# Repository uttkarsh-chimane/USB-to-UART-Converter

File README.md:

<h1 align="center">💡 USB Type-C to UART Converter</h1>

---

## ⚙️ What I Built

A compact, production-style USB-to-UART bridge designed in KiCad using the CP2102N USB-to-serial interface IC.

The board enables reliable serial communication between a host PC and embedded systems for debugging, firmware flashing, and data exchange. It is designed as a plug-and-play development tool that replaces generic USB-to-UART adapters with a cleaner, integrated hardware solution.

--- 

## 🚀 Overview

This project implements a robust USB-to-UART hardware interface using a USB Type-C connector and the CP2102N USB bridge IC.

---

## 📷 Project Gallery

🧩 **3D PCB Render**

Final assembled board visualization from KiCad 3D viewer.

🟠 **PCB Layout – Top Copper**

Top layer routing showing USB interface, CP2102N placement, and signal routing.

.png)

🔵 **PCB Layout – Bottom Copper**

Bottom layer used for ground plane and signal return integrity.

.png)

⚙️ **Schematic – Power Section**

Power input stage including USB VBUS handling, decoupling, and regulation strategy.

🔌 **Schematic – USB Interface Section**

USB Type-C interface with CC resistors, ESD protection, and data routing.

📡 **Schematic – UART Interface Section**

CP2102N UART communication block with TX/RX routing and headers.

---

## ✨ Features

* USB Type-C interface (USB 2.0)
* CP2102N USB-to-UART bridge IC
* TX/RX UART communication support
* RX/TX status indicator LEDs
* USB data line ESD protection
* Compact 2-layer PCB design
* Dedicated UART breakout header
* USB-powered operation (5V VBUS input)

---

## ⚒️ Hardware Architecture

```
USB Type-C
     │
     ▼
ESD Protection
     │
     ▼
CP2102N USB-to-UART Bridge
     │
     ▼
UART Header (TX, RX, GND, VBUS, RST)

```

---

## 🧠 Schematic Highlights

**USB Type-C Interface**

* USB 2.0 Type-C receptacle used
* CC1 and CC2 configured with 5.1kΩ pull-down resistors
* D+ and D− routed directly to CP2102N
* ESD protection added to improve robustness against hot-plug events and electrostatic discharge

**CP2102N Interface**

* Handles USB enumeration and serial conversion
* Powered directly from USB VBUS (5V)
* Decoupling capacitors placed close to power pins for stability
* Designed for stable and noise-resistant communication

**UART Header**

The board exposes a standard UART interface for external devices:

| Pin  | Function      |
| ---- | ------------- |
| GND  | Ground        |
| VBUS | 5V Supply     |
| RX   | UART Receive  |
| TX   | UART Transmit |
| RST  | Reset Line    |

---

## 🧩 PCB Design Insights

**Layout Strategy**

* Compact footprint optimized for embedded use
* USB connector placed at PCB edge for accessibility
* Solid ground plane for improved signal integrity
* Clear separation between power and signal routing

**Routing Strategy**

* USB D+ / D− routed as a differential pair
* Short and direct trace routing for signal integrity
* Decoupling capacitors placed close to IC power pins
* Continuous ground reference used to minimize noise

---

## 🧪 Applications

* MCU flashing (ESP32, STM32, AVR, etc.)
* Embedded system debugging
* Serial terminal communication
* IoT development workflows
* Firmware logging and monitoring

---

## ⚠️ Limitations

* No galvanic isolation (direct USB ground connection)
* Fixed logic levels (no onboard level shifting)
* USB-powered only (no external power input)
* No auto-reset circuitry for ESP-class boards

---

## 🚀 Future Improvements

* Auto-reset support for ESP-based boards
* Switchable 3.3V / 5V logic levels
* Onboard LDO regulator for cleaner power rail
* Polyfuse protection for overcurrent safety
* Test pads for signal debugging
* Enhanced EMI/ESD protection stage

---

## 🎓 Learning Outcomes

This project demonstrates practical experience in:

* KiCad schematic and PCB design workflow
* USB 2.0 hardware implementation
* CP2102N integration and configuration
* High-speed signal routing fundamentals
* Power integrity and decoupling design
* Ground plane design methodology

---

## 🛠️ Design Software

* KiCad 10 (Schematic + PCB Layout + 3D Render)

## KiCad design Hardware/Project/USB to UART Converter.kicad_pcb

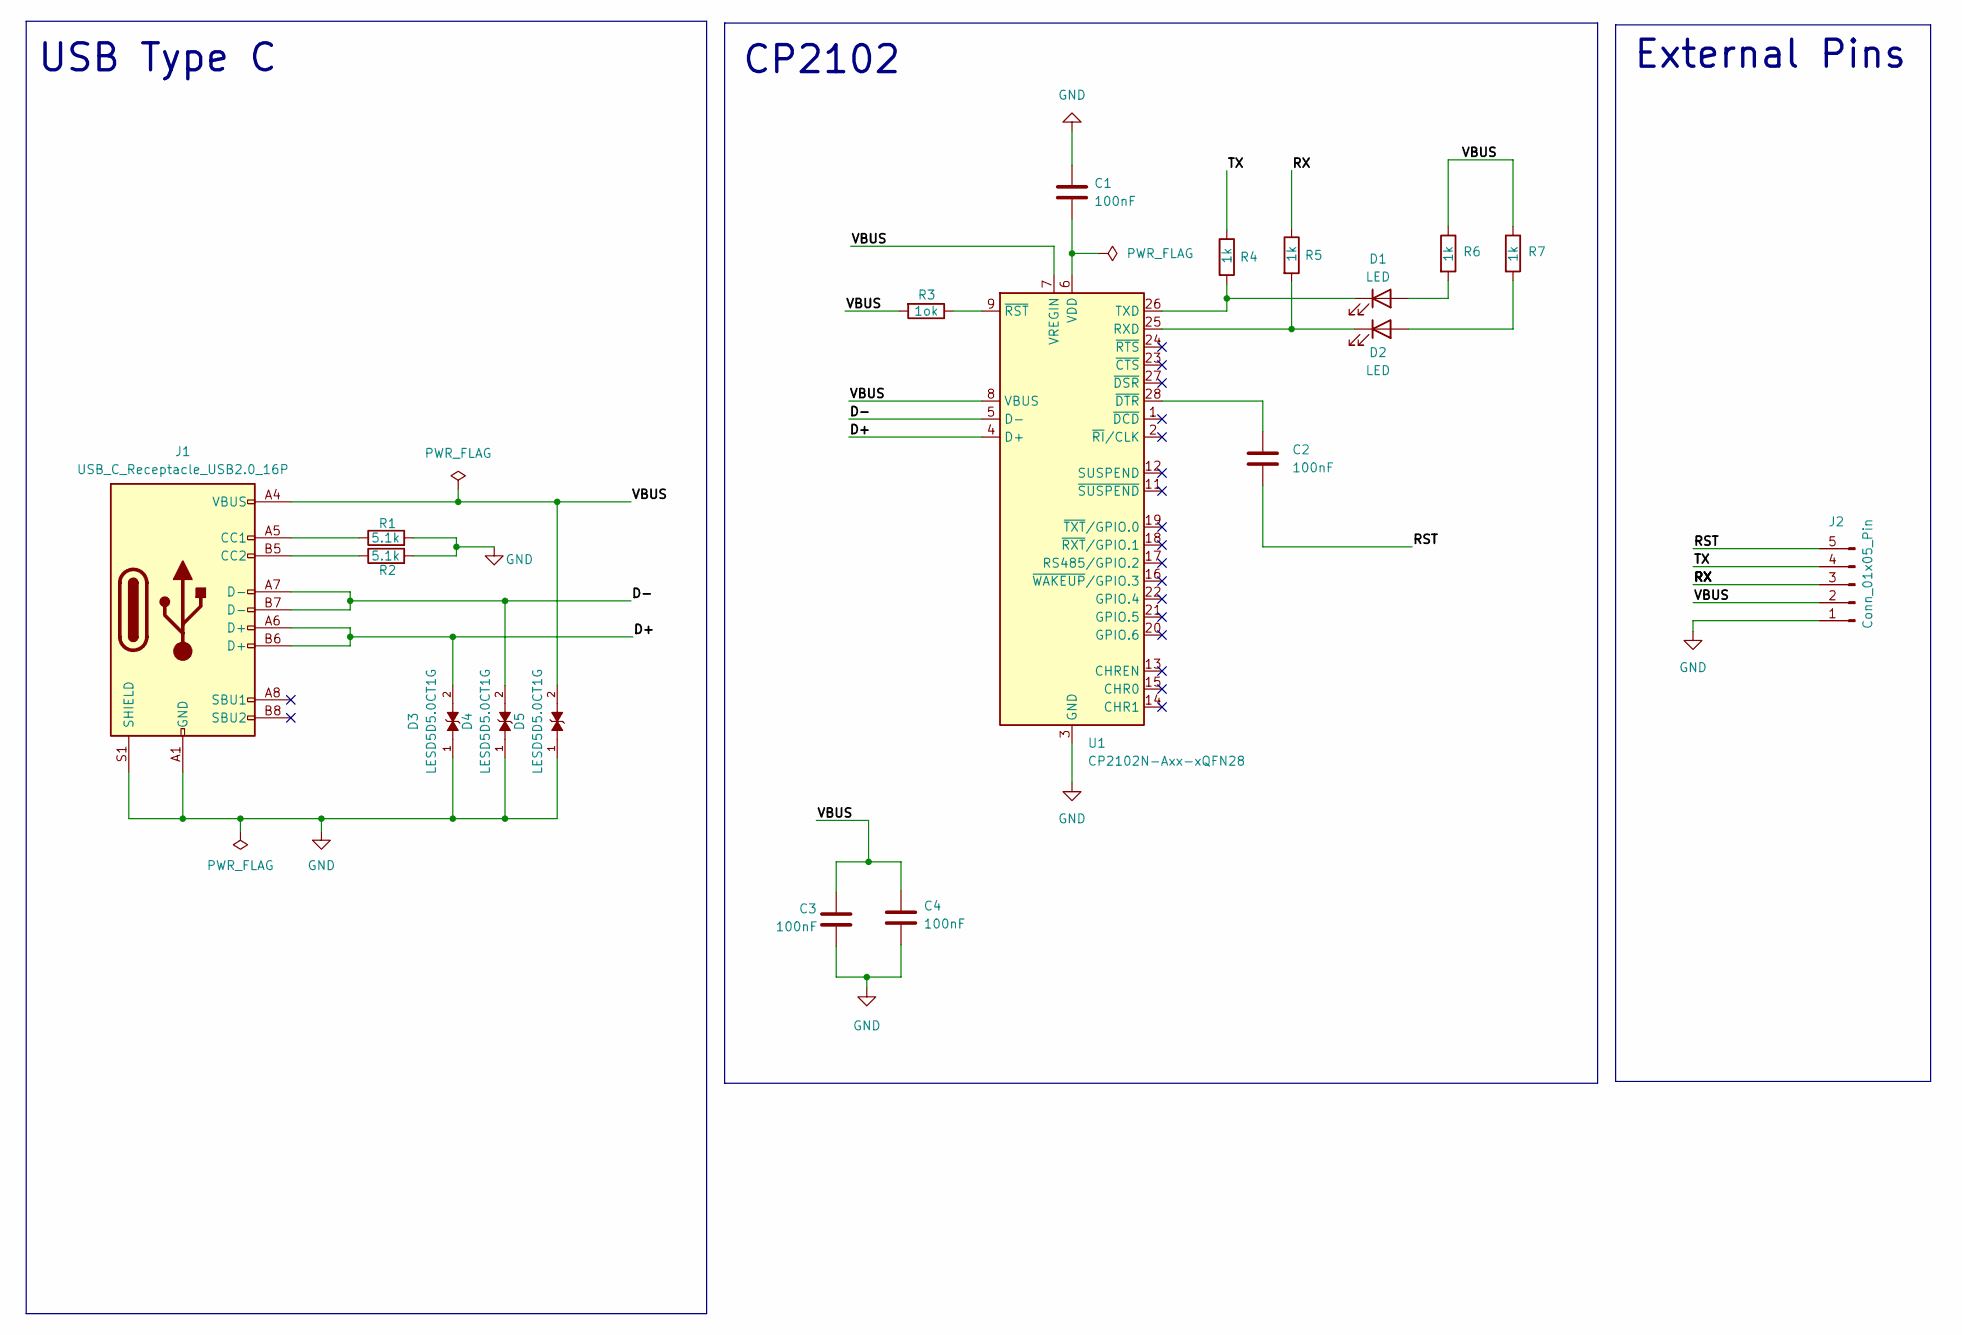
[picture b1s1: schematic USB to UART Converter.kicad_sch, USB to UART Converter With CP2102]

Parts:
C1, C2, C3, C4: 100nF; C_0201_0603Metric
D1, D2: LED; LED_0201_0603Metric
D3, D4, D5: LESD5D5.0CT1G; TVS_LESD5D5.0CT1G; PARTREV O
J1: USB_C_Receptacle_USB2.0_16P; USB_C_Receptacle_HRO_TYPE-C-31-M-12
J2: Conn_01x05_Pin; PinHeader_1x05_P2.54mm_Horizontal
R1, R2: 5.1k; R_0201_0603Metric
R3: 1ok; R_0201_0603Metric
R4, R5, R6, R7: 1k; R_0201_0603Metric
U1: CP2102N-Axx-xQFN28; QFN-28-1EP_5x5mm_P0.5mm_EP3.35x3.35mm

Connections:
/D+: D3.2, J1.A6 (D+), J1.B6 (D+), U1.4 (D+)
/D-: D4.2, J1.A7 (D-), J1.B7 (D-), U1.5 (D-)
/RST: C2.2, J2.5
/RX: J2.3, R5.1
/TX: J2.4, R4.1
/VBUS: C3.1, C4.1, D5.2, J1.A4 (VBUS), J1.A9 (VBUS), J1.B4 (VBUS), J1.B9 (VBUS), J2.2, R3.2, R6.1, R7.1, U1.7 (VREGIN), U1.8 (VBUS)
GND: C1.1, C3.2, C4.2, D3.1, D4.1, D5.1, J1.A1 (GND), J1.A12 (GND), J1.B1 (GND), J1.B12 (GND), J1.S1 (SHIELD), J2.1, R1.2, R2.2, U1.3 (GND), U1.29 (GND)
unnamed: D1.2 (A), R6.2
unnamed: D1.1 (K), R4.2, U1.26 (TXD)
unnamed: D2.2 (A), R7.2
unnamed: D2.1 (K), R5.2, U1.25 (RXD)
unnamed: J1.A5 (CC1), R1.1
unnamed: J1.B5 (CC2), R2.1
unnamed: C1.2, U1.6 (VDD)
unnamed: C2.1, U1.28 (~DTR)
unnamed: R3.1, U1.9 (~RST)

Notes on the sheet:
CP2102
External Pins
USB Type C

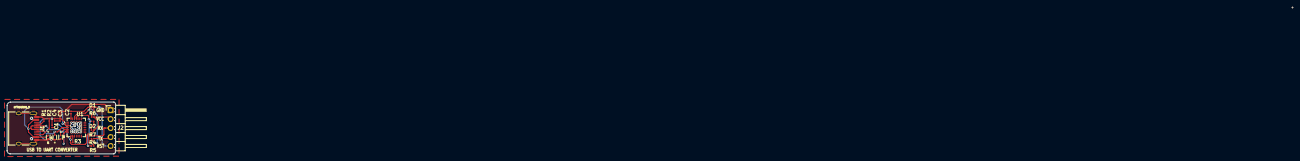
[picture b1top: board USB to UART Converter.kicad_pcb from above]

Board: 2 copper layers, 30.8 x 14.7 mm, 19 parts (0 on the bottom side), 16 nets.

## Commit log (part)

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2026-05-30 Initial commit: USB to UART converter hardware project
